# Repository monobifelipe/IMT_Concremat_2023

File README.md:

# IMT_Concremat_2023
 Repositório de códigos desenvolvidos no Instituto Mauá de Tecnlogia em parceria com a Concremat para monitoramento de estruturas.

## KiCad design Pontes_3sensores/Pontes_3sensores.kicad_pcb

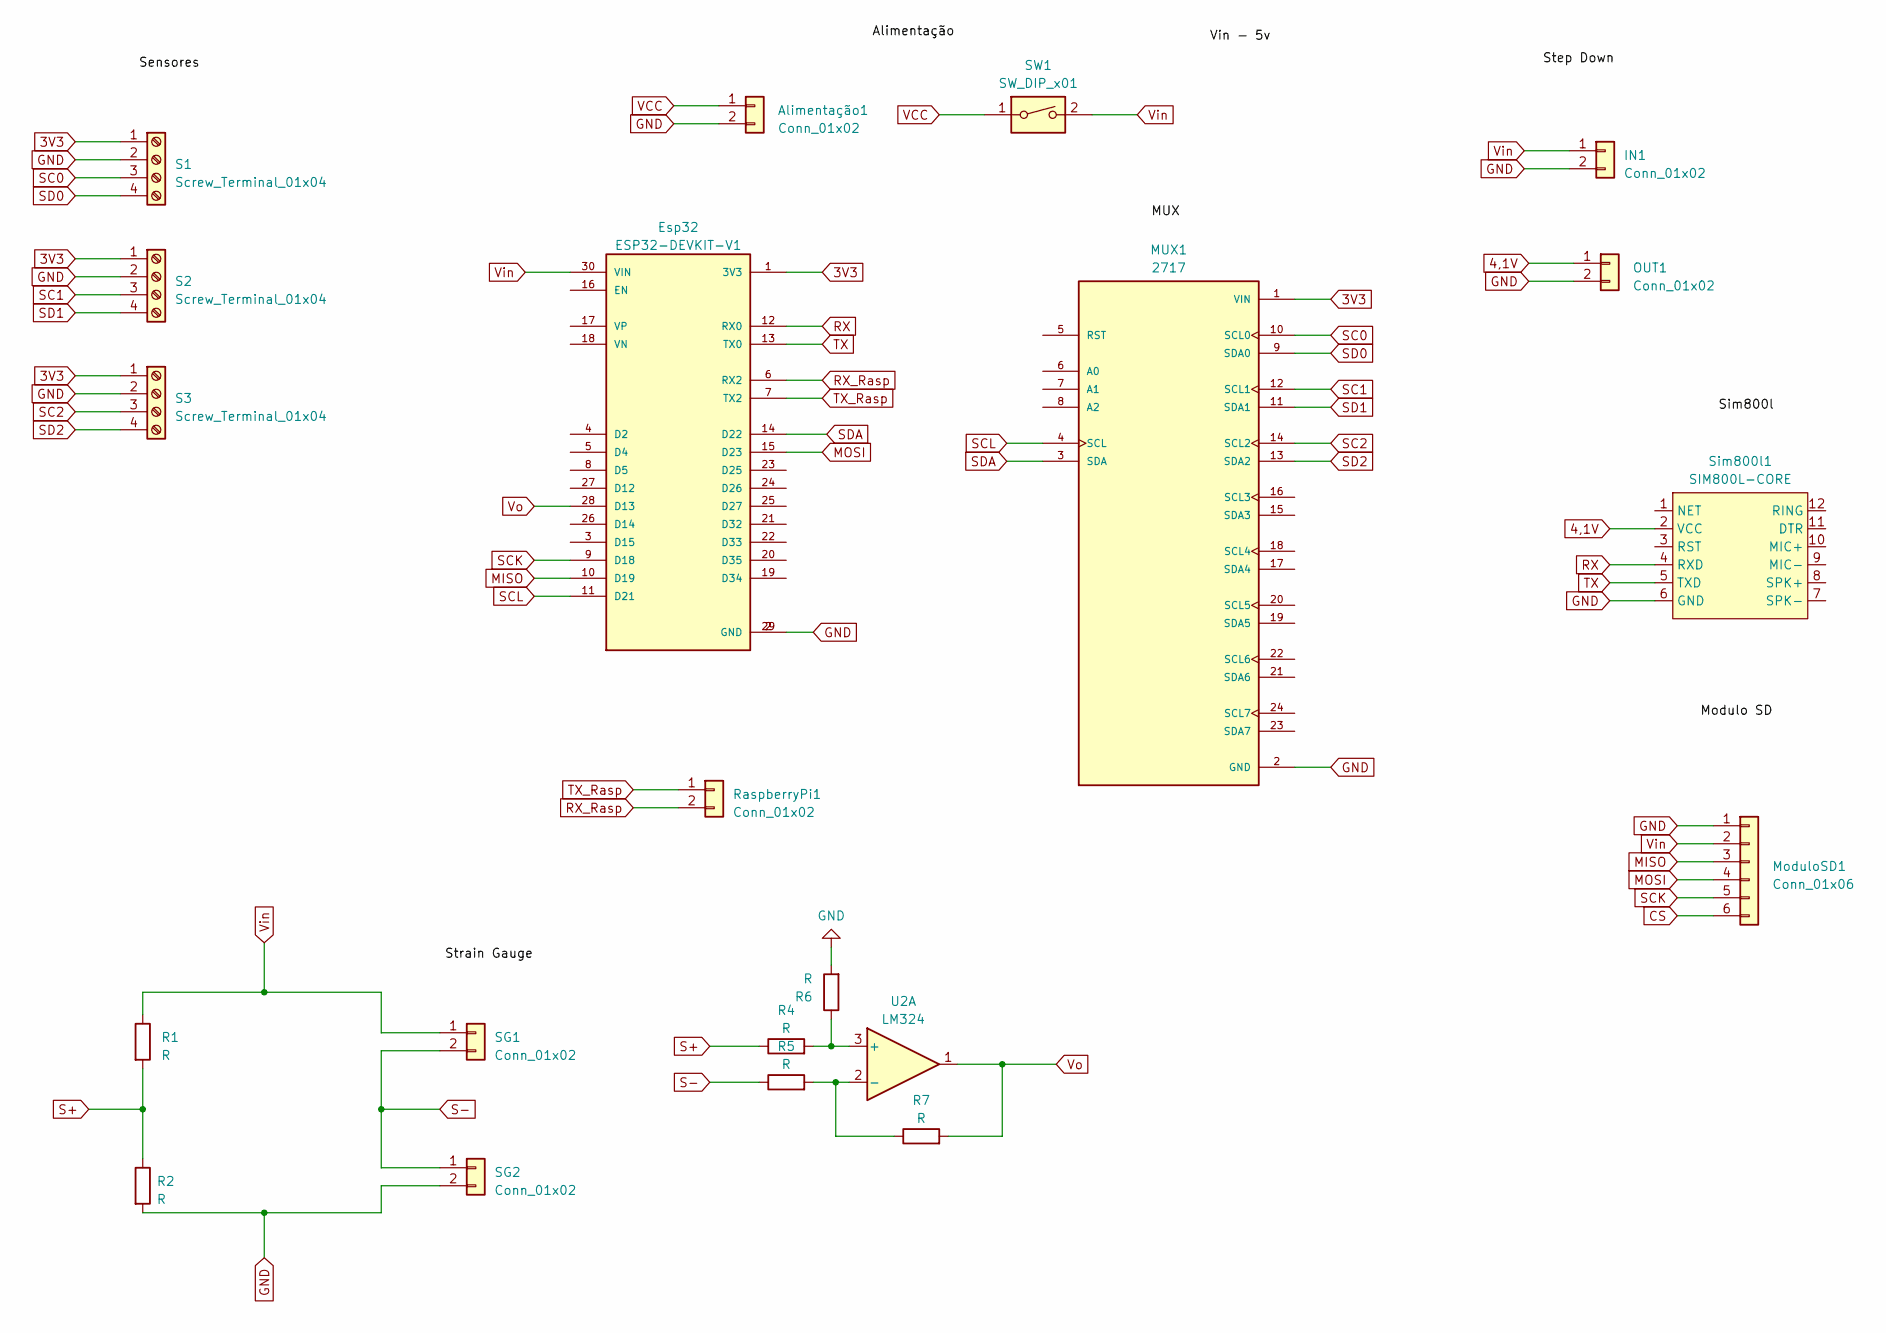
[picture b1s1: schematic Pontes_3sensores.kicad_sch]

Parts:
Alimentação1: Conn_01x02; TerminalBlock_4Ucon_1x02_P3.50mm_Horizontal
Esp32: ESP32-DEVKIT-V1; MODULE_ESP32_DEVKIT_V1; PARTREV N/A
IN1: Conn_01x02; TerminalBlock_4Ucon_1x02_P3.50mm_Horizontal
MUX1: 2717; MODULE_2717; PARTREV Sep 11, 2015
ModuloSD1: Conn_01x06; PinHeader_1x06_P2.54mm_Vertical
OUT1: Conn_01x02; TerminalBlock_4Ucon_1x02_P3.50mm_Horizontal
R1, R2, R4, R5, R6, R7: R; R_Axial_DIN0207_L6.3mm_D2.5mm_P10.16mm_Horizontal
RaspberryPi1: Conn_01x02; TerminalBlock_4Ucon_1x02_P3.50mm_Horizontal
S1, S2, S3: Screw_Terminal_01x04; TerminalBlock_4Ucon_1x04_P3.50mm_Horizontal
SG1, SG2: Conn_01x02; TerminalBlock_4Ucon_1x02_P3.50mm_Horizontal
SW1: SW_DIP_x01; SW_Slide_1P2T_CK_OS102011MS2Q
Sim800l1: SIM800L-CORE
U2: LM324; DIP-14_W7.62mm

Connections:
3V3: Esp32.1 (3V3), MUX1.1 (VIN), S1.1, S2.1, S3.1
4,1V: OUT1.1, Sim800l1.2 (VCC)
CS: ModuloSD1.6
GND: Alimentação1.2, Esp32.2 (GND), Esp32.29 (GND), IN1.2, MUX1.2 (GND), ModuloSD1.1, OUT1.2, R2.2, R6.2, S1.2, S2.2, S3.2, SG2.2, Sim800l1.6 (GND), U2.11 (V-); also elsewhere on the board
MISO: Esp32.10 (D19), ModuloSD1.3
MOSI: Esp32.15 (D23), ModuloSD1.4
unnamed: R4.2, R6.1, U2.3 (+)
unnamed: R5.2, R7.1, U2.2 (-)
RX: Esp32.12 (RX0), Sim800l1.4 (RXD)
RX_Rasp: Esp32.6 (RX2), RaspberryPi1.2
S+: R1.2, R2.1, R4.1
S-: R5.1, SG1.2, SG2.1; also elsewhere on the board
SC0: MUX1.10 (SCL0), S1.3
SC1: MUX1.12 (SCL1), S2.3
SC2: MUX1.14 (SCL2), S3.3
SCK: Esp32.9 (D18), ModuloSD1.5
SCL: Esp32.11 (D21), MUX1.4 (SCL)
SD0: MUX1.9 (SDA0), S1.4
SD1: MUX1.11 (SDA1), S2.4
SD2: MUX1.13 (SDA2), S3.4
SDA: Esp32.14 (D22), MUX1.3 (SDA)
TX: Esp32.13 (TX0), Sim800l1.5 (TXD)
TX_Rasp: Esp32.7 (TX2), RaspberryPi1.1
VCC: Alimentação1.1, SW1.1
Vin: Esp32.30 (VIN), IN1.1, ModuloSD1.2, R1.1, SG1.1, SW1.2, U2.4 (V+)
Vo: Esp32.28 (D13), R7.2, U2.1

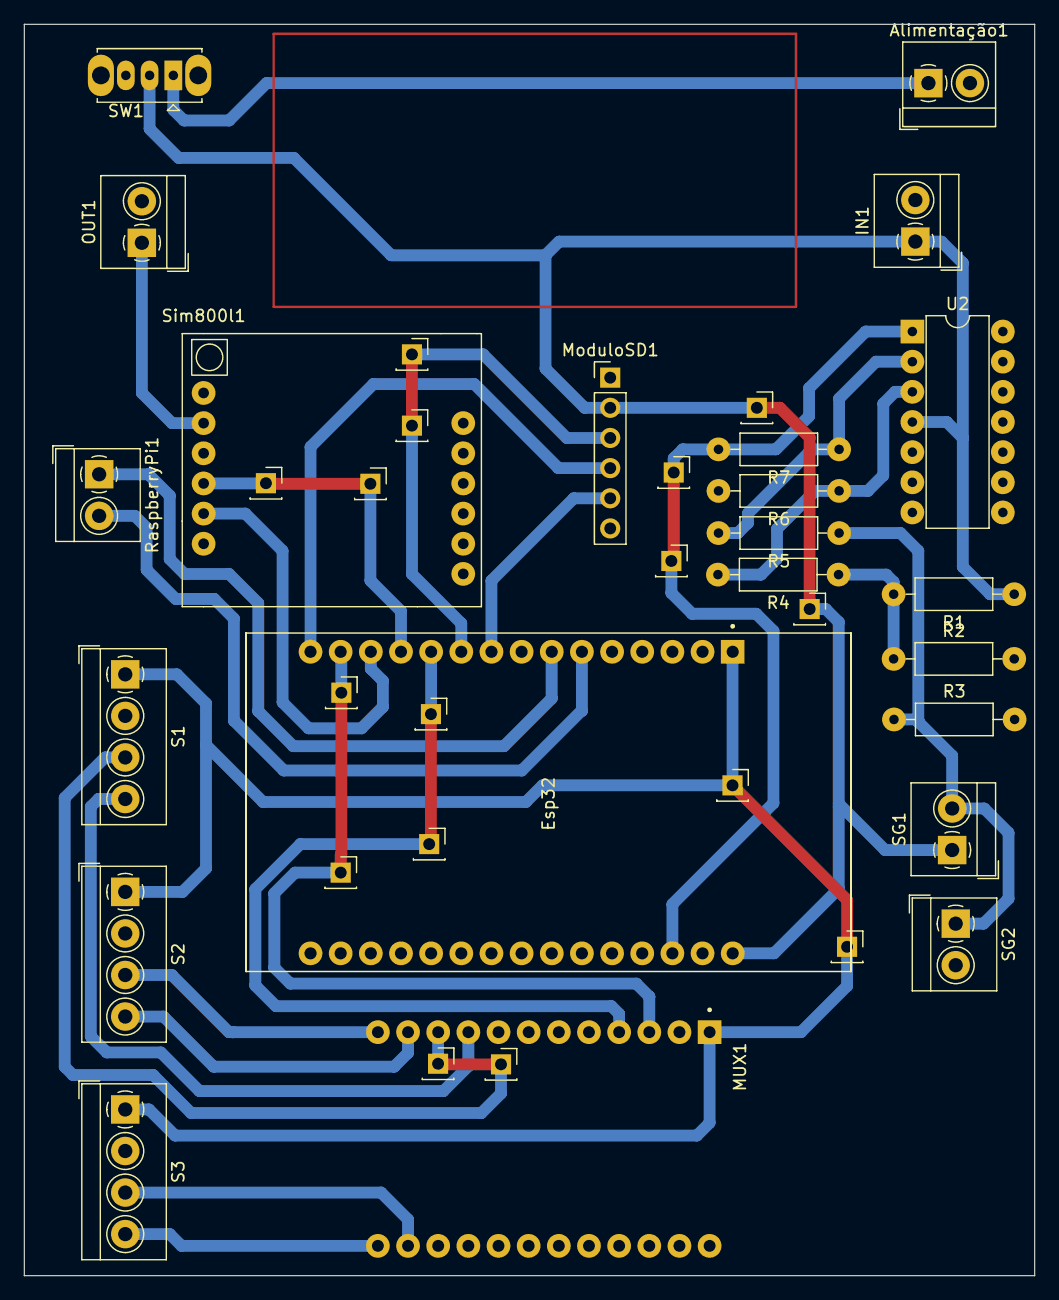
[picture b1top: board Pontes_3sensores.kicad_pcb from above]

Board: 2 copper layers, 85.1 x 105.4 mm, 22 parts (0 on the bottom side), 25 nets.

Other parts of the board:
R3: R; R_Axial_DIN0207_L6.3mm_D2.5mm_P10.16mm_Horizontal

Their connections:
GND: R3.2; also elsewhere on the board
S-: R3.1; also elsewhere on the board

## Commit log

2023-09-21 Accelerometer_test_code
    Código para teste de acelerômetro.
2023-09-21 FFT_Accelerometer_Test_Code
    Código para teste de FFT.
2023-10-10 Inclusão de código teste para strain gauge
2023-10-10 Commit dos códigos completos
2023-10-11 Pasta com projeto de placa eletrônica
